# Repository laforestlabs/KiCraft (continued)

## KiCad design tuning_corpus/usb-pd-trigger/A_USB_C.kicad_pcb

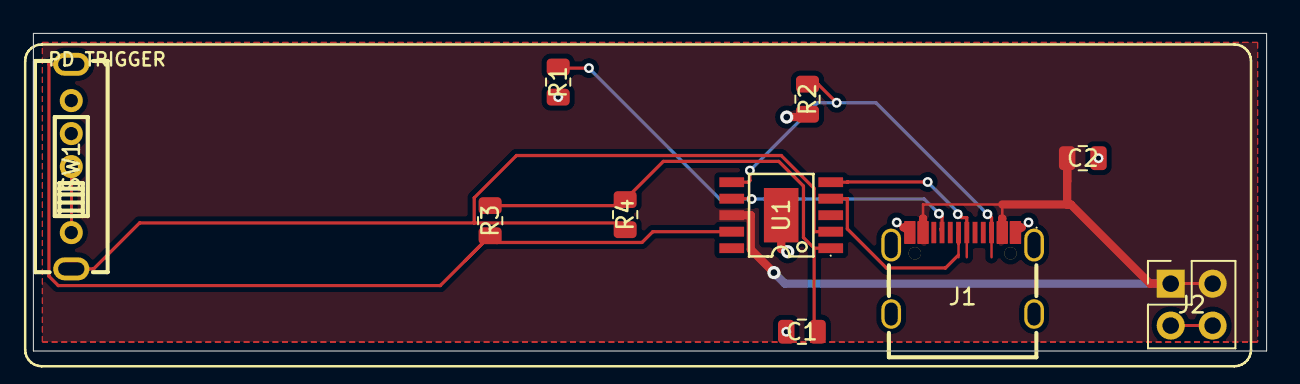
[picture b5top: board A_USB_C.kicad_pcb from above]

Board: 2 copper layers, 74.7 x 19.2 mm, 10 parts (0 on the bottom side), 9 nets.

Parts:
C1: 1ÂµF; C_0805_2012Metric
C2: 10ÂµF; C_0805_2012Metric
J1: USB-C 16P Receptacle; USB-C_SMD-TYPE-C-31-M-12_1
J2: Pin Header 2x02; PinHeader_2x02_P2.54mm_Vertical
R1, R2: 5.1k; R_0805_2012Metric
R3, R4: 47k; R_0805_2012Metric
SW1: 3-Position DPDT Slide Switch; SW-TH_SS13D07VG4
U1: CH224K; ESSOP-10_L4.9-W3.9-P1.0-LS6.0-TL-EP

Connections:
CC1: J1.A5, R1.1, U1.7
CC2: J1.B5, R2.1, U1.6
CFG1: R3.2, SW1.5, U1.9
CFG2: R4.2, SW1.6, U1.2
DM_LOCAL: J1.A7, U1.5
DP_LOCAL: J1.A6, U1.4
GND: C1.2, C2.2, J1.1, J1.2, J1.3, J1.4, J1.A1B12, J1.B1A12, J2.3, J2.4, R1.2, R2.2, SW1.1, SW1.2, SW1.4, U1.11
VDD: C1.1, R3.1, R4.1, U1.1
VOUT: C2.1, J1.A4B9, J1.B4A9, J2.1, J2.2, U1.8

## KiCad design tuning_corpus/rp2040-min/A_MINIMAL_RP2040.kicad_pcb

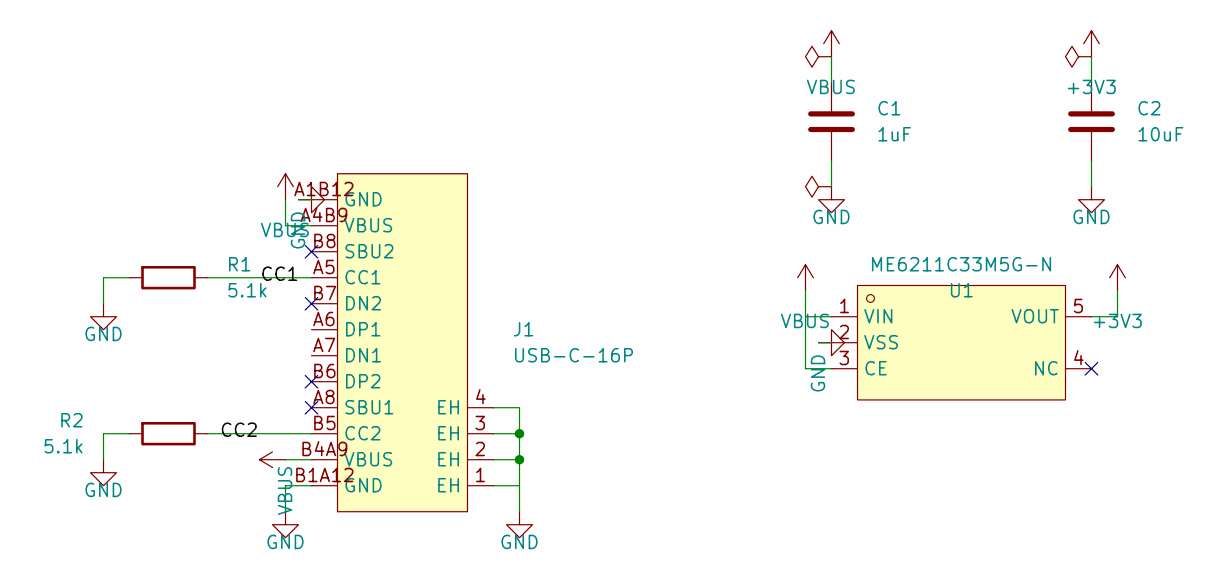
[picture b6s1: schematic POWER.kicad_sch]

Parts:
C1: 1uF; C_0805_2012Metric
C2: 10uF; C_0805_2012Metric
J1: USB-C-16P; USB-C_SMD-TYPE-C-31-M-12_1
R1, R2: 5.1k; R_0805_2012Metric
U1: ME6211C33M5G-N; SOT-23-5_L3.0-W1.7-P0.95-LS2.8-BL

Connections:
CC1: J1.A5 (CC1), R1.1
CC2: J1.B5 (CC2), R2.1
USB_DM: J1.A7 (DN1); also elsewhere on the board
USB_DP: J1.A6 (DP1); also elsewhere on the board

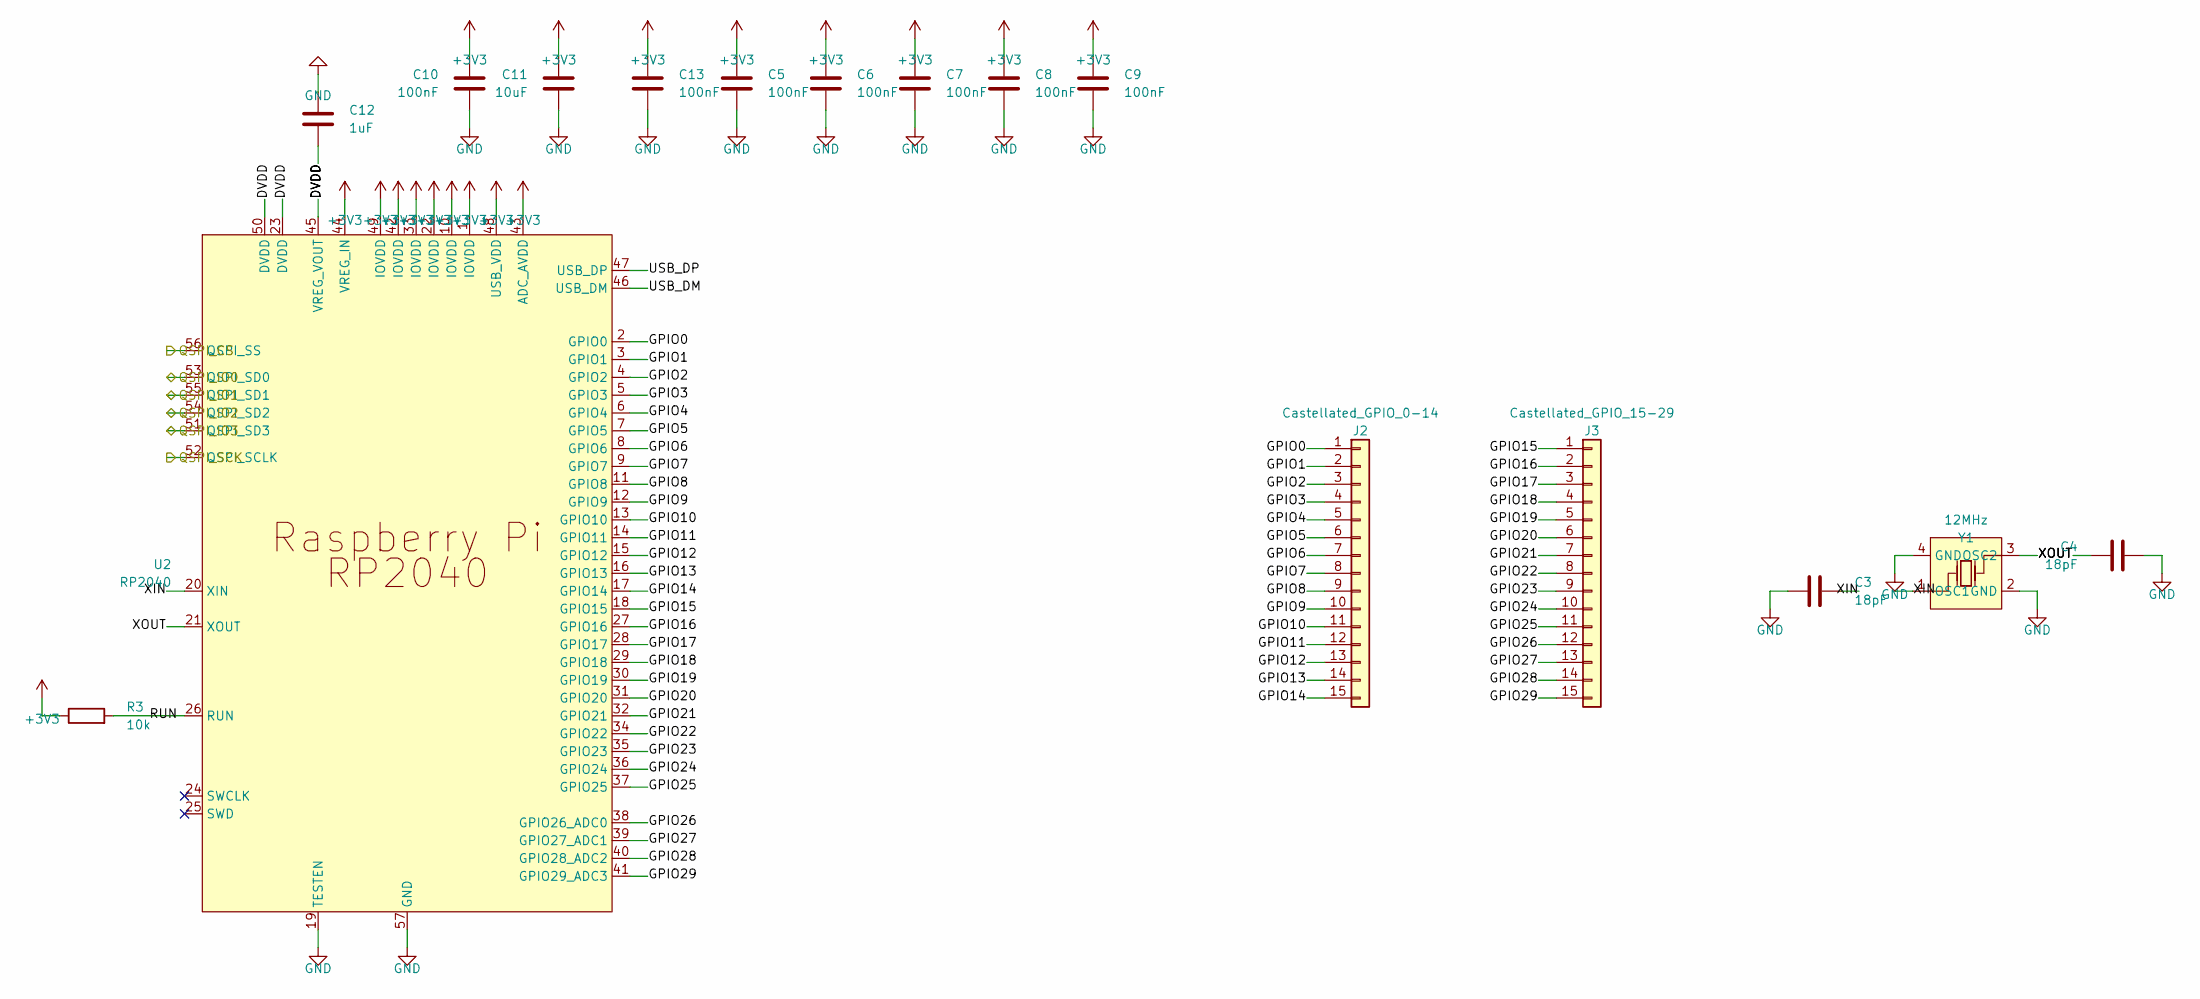
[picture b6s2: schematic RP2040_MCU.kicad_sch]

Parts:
C3, C4: 18pF; C_0805_2012Metric
C5, C6, C7, C8, C9, C10, C13: 100nF; C_0805_2012Metric
C11: 10uF; C_0805_2012Metric
C12: 1uF; C_0805_2012Metric
J2: Castellated_GPIO_0-14; PinHeader_1x15_P2.54mm_Vertical
J3: Castellated_GPIO_15-29; PinHeader_1x15_P2.54mm_Vertical
R3: 10k; R_0805_2012Metric
U2: RP2040; LQFN-56_L7.0-W7.0-P0.4-EP
Y1: 12MHz; CRYSTAL-SMD_4P-L3.2-W2.5-BL

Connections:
DVDD: C12.1, U2.23 (DVDD), U2.45 (VREG_VOUT), U2.50 (DVDD)
GPIO0: J2.1, U2.2 (GPIO0)
GPIO1: J2.2, U2.3 (GPIO1)
GPIO2: J2.3, U2.4 (GPIO2)
GPIO3: J2.4, U2.5 (GPIO3)
GPIO4: J2.5, U2.6 (GPIO4)
GPIO5: J2.6, U2.7 (GPIO5)
GPIO6: J2.7, U2.8 (GPIO6)
GPIO7: J2.8, U2.9 (GPIO7)
GPIO8: J2.9, U2.11 (GPIO8)
GPIO9: J2.10, U2.12 (GPIO9)
GPIO10: J2.11, U2.13 (GPIO10)
GPIO11: J2.12, U2.14 (GPIO11)
GPIO12: J2.13, U2.15 (GPIO12)
GPIO13: J2.14, U2.16 (GPIO13)
GPIO14: J2.15, U2.17 (GPIO14)
GPIO15: J3.1, U2.18 (GPIO15)
GPIO16: J3.2, U2.27 (GPIO16)
GPIO17: J3.3, U2.28 (GPIO17)
GPIO18: J3.4, U2.29 (GPIO18)
GPIO19: J3.5, U2.30 (GPIO19)
GPIO20: J3.6, U2.31 (GPIO20)
GPIO21: J3.7, U2.32 (GPIO21)
GPIO22: J3.8, U2.34 (GPIO22)
GPIO23: J3.9, U2.35 (GPIO23)
GPIO24: J3.10, U2.36 (GPIO24)
GPIO25: J3.11, U2.37 (GPIO25)
GPIO26: J3.12, U2.38 (GPIO26_ADC0)
GPIO27: J3.13, U2.39 (GPIO27_ADC1)
GPIO28: J3.14, U2.40 (GPIO28_ADC2)
GPIO29: J3.15, U2.41 (GPIO29_ADC3)
QSPI_CS: U2.56 (QSPI_SS); also elsewhere on the board
QSPI_IO0: U2.53 (QSPI_SD0); also elsewhere on the board
QSPI_IO1: U2.55 (QSPI_SD1); also elsewhere on the board
QSPI_IO2: U2.54 (QSPI_SD2); also elsewhere on the board
QSPI_IO3: U2.51 (QSPI_SD3); also elsewhere on the board
QSPI_SCK: U2.52 (QSPI_SCLK); also elsewhere on the board
RUN: R3.2, U2.26 (RUN)
USB_DM: U2.46 (USB_DM); also elsewhere on the board
USB_DP: U2.47 (USB_DP); also elsewhere on the board
XIN: C3.1, U2.20 (XIN), Y1.1 (OSC1)
XOUT: C4.1, U2.21 (XOUT), Y1.3 (OSC2)

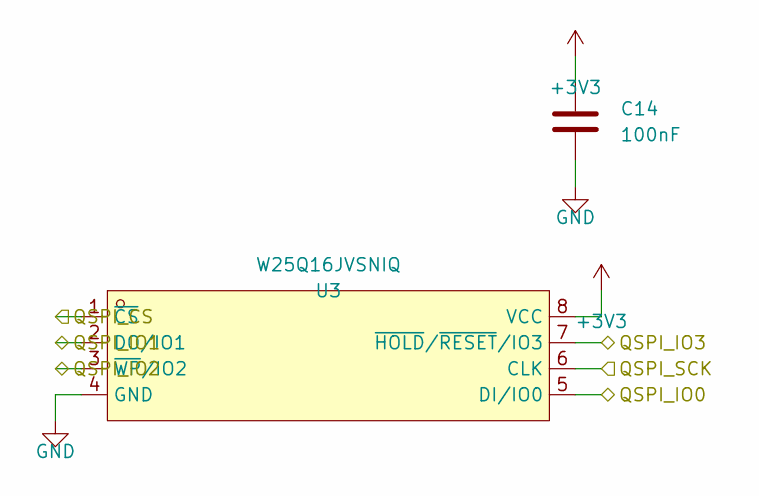
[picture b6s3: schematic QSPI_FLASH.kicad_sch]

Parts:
C14: 100nF; C_0805_2012Metric
U3: W25Q16JVSNIQ; SOP-8_L4.9-W3.9-P1.27-LS6.0-BL

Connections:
QSPI_CS: U3.1 (~CS); also elsewhere on the board
QSPI_IO0: U3.5 (DI/IO0); also elsewhere on the board
QSPI_IO1: U3.2 (DO/IO1); also elsewhere on the board
QSPI_IO2: U3.3 (~WP/IO2); also elsewhere on the board
QSPI_IO3: U3.7 (~HOLD/~RESET/IO3); also elsewhere on the board
QSPI_SCK: U3.6 (CLK); also elsewhere on the board

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
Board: 2 copper layers, 24 parts (0 on the bottom side), 47 nets, no tracks yet.

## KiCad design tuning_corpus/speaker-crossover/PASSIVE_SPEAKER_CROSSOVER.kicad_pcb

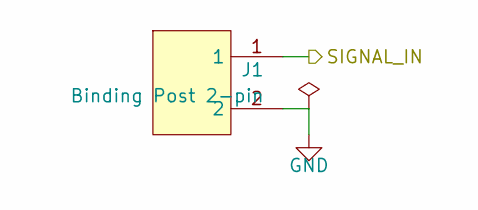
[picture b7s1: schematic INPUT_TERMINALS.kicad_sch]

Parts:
J1: Binding Post 2-pin; CONN-TH_WJ126V-5.0-2P

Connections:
GND: J1.2; also elsewhere on the board
SIGNAL_IN: J1.1; also elsewhere on the board

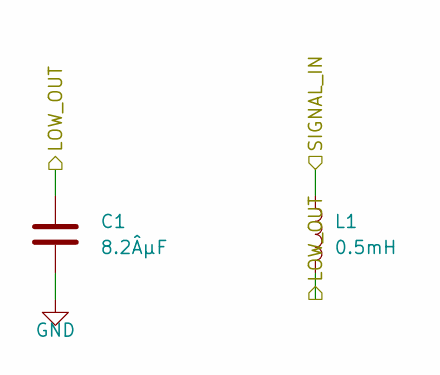
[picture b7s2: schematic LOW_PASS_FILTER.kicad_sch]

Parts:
C1: 8.2ÂµF; C_Radial_D10.0mm_H12.5mm_P5.00mm
L1: 0.5mH; L_Radial_D12.0mm_P5.00mm_Fastron_11P

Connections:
GND: C1.2; also elsewhere on the board
LOW_OUT: C1.1, L1.2; also elsewhere on the board
SIGNAL_IN: L1.1; also elsewhere on the board

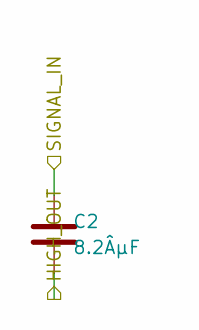
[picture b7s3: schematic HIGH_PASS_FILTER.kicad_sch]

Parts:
C2: 8.2ÂµF; C_Radial_D10.0mm_H12.5mm_P5.00mm

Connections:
HIGH_OUT: C2.2; also elsewhere on the board
SIGNAL_IN: C2.1; also elsewhere on the board

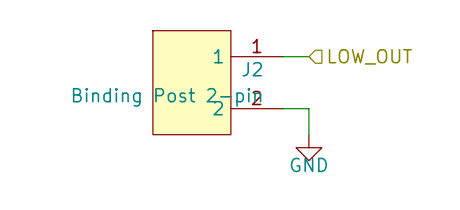
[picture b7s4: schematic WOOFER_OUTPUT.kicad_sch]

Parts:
J2: Binding Post 2-pin; CONN-TH_WJ126V-5.0-2P

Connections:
GND: J2.2; also elsewhere on the board
LOW_OUT: J2.1; also elsewhere on the board

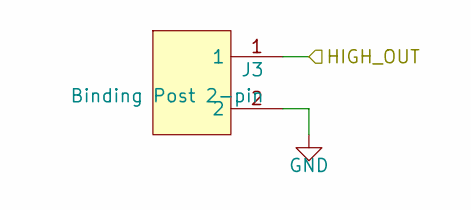
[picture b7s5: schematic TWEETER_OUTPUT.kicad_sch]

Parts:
J3: Binding Post 2-pin; CONN-TH_WJ126V-5.0-2P

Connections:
GND: J3.2; also elsewhere on the board
HIGH_OUT: J3.1; also elsewhere on the board

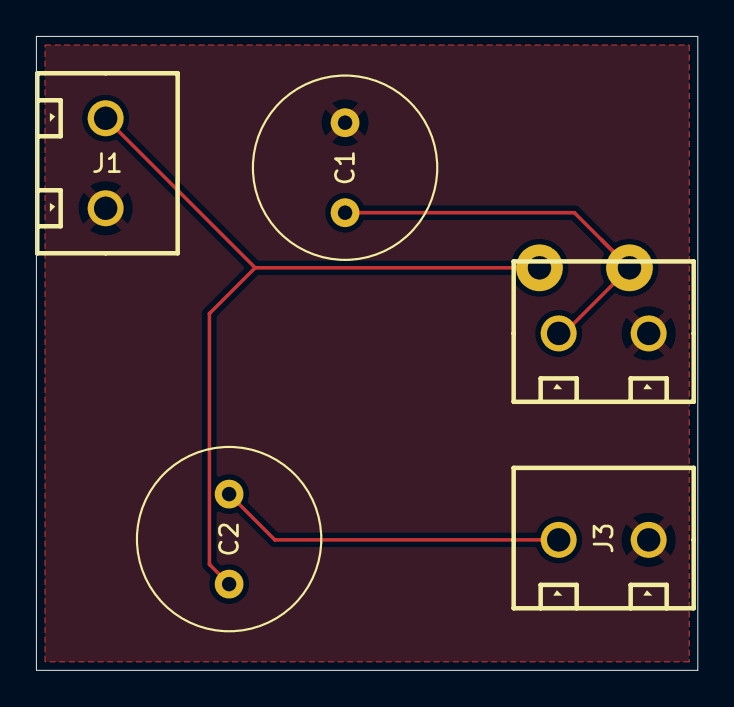
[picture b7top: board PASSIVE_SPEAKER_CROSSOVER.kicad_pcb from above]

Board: 2 copper layers, 36.7 x 35.2 mm, 6 parts (1 on the bottom side), 4 nets.

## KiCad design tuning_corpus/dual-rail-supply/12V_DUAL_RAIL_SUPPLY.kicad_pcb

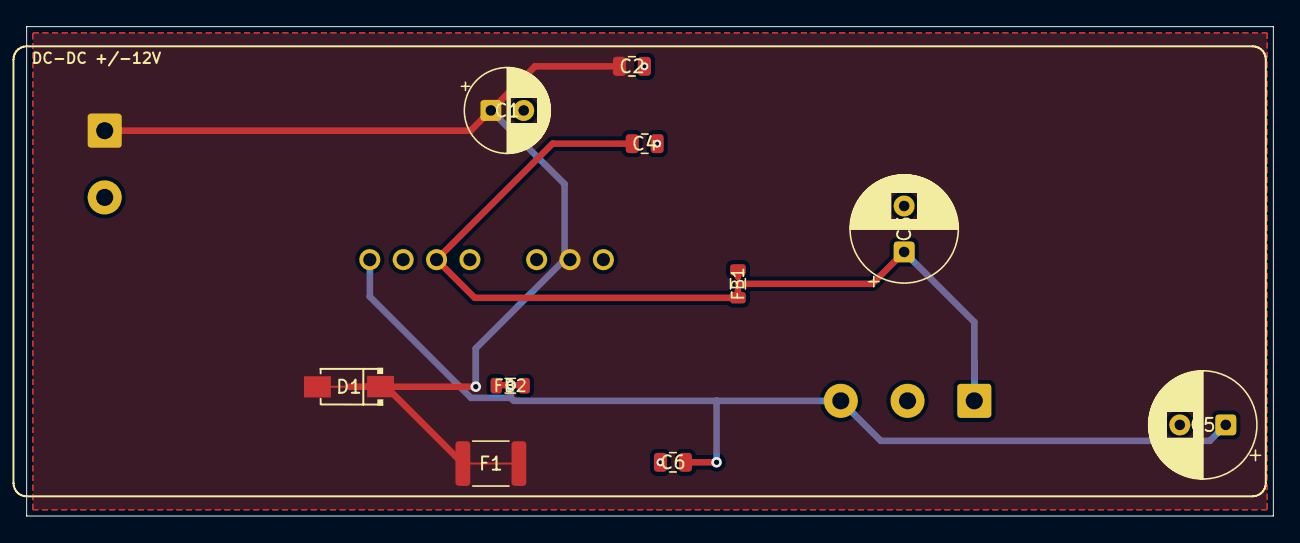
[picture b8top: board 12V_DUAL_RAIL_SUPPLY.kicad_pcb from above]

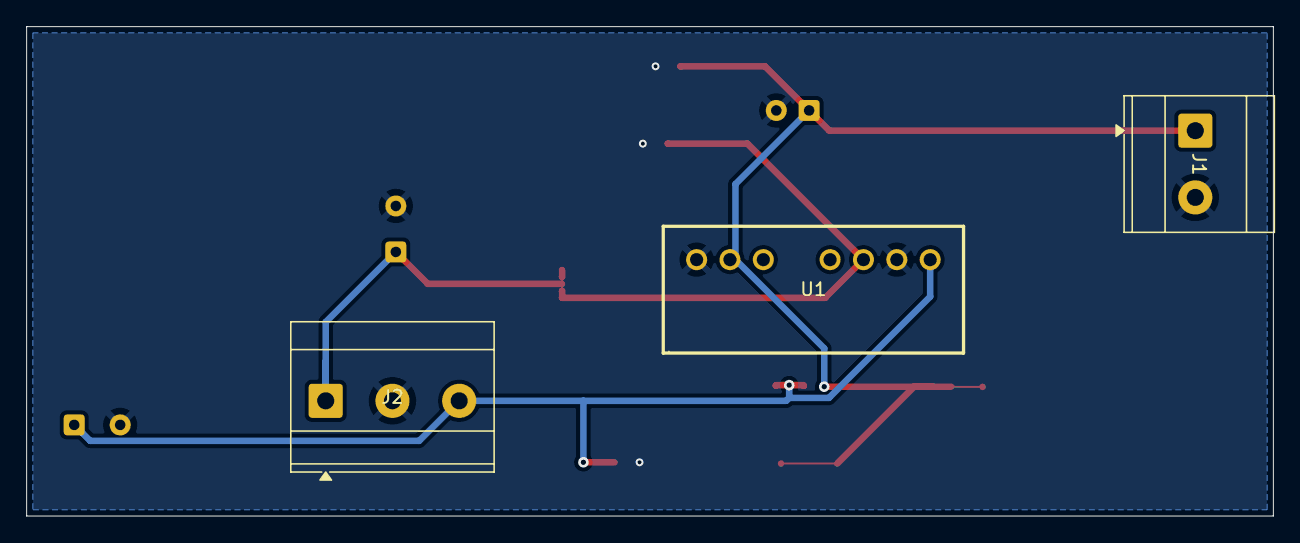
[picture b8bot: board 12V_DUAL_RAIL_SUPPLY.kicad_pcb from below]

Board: 2 copper layers, 94.9 x 37.3 mm, 13 parts (3 on the bottom side), 4 nets.

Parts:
C1: 100ÂµF 35V; CP_Radial_D6.3mm_P2.50mm
C2, C4, C6: 0.1ÂµF; C_0805_2012Metric
C3, C5: 470ÂµF 16V; CP_Radial_D8.0mm_P3.50mm
D1: SS14; SMA_L4.3-W2.6-LS5.0-RD
F1: 200mA PTC; Fuse_1812_4532Metric
FB1, FB2: Ferrite Bead; L_0805_2012Metric
J1: 2-pin 5.08mm; TerminalBlock_Phoenix_MKDS-3-2-5.08_1x02_P5.08mm_Horizontal
J2: 3-pin 5.08mm; TerminalBlock_Phoenix_MKDS-3-3-5.08_1x03_P5.08mm_Horizontal
U1: WRA2412S-3WR2; PWRM-TH_WRAXXXXS-3WR2

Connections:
+12V: C3.1, C4.1, FB1.1, FB1.2, J2.1, U1.6
+24V: C1.1, C2.1, D1.1, D1.2, F1.1, F1.2, J1.1, U1.2
-12V: C5.1, C6.1, FB2.1, FB2.2, J2.3, U1.8
GND: C1.2, C2.2, C3.2, C4.2, C5.2, C6.2, J1.2, J2.2, U1.1, U1.7
